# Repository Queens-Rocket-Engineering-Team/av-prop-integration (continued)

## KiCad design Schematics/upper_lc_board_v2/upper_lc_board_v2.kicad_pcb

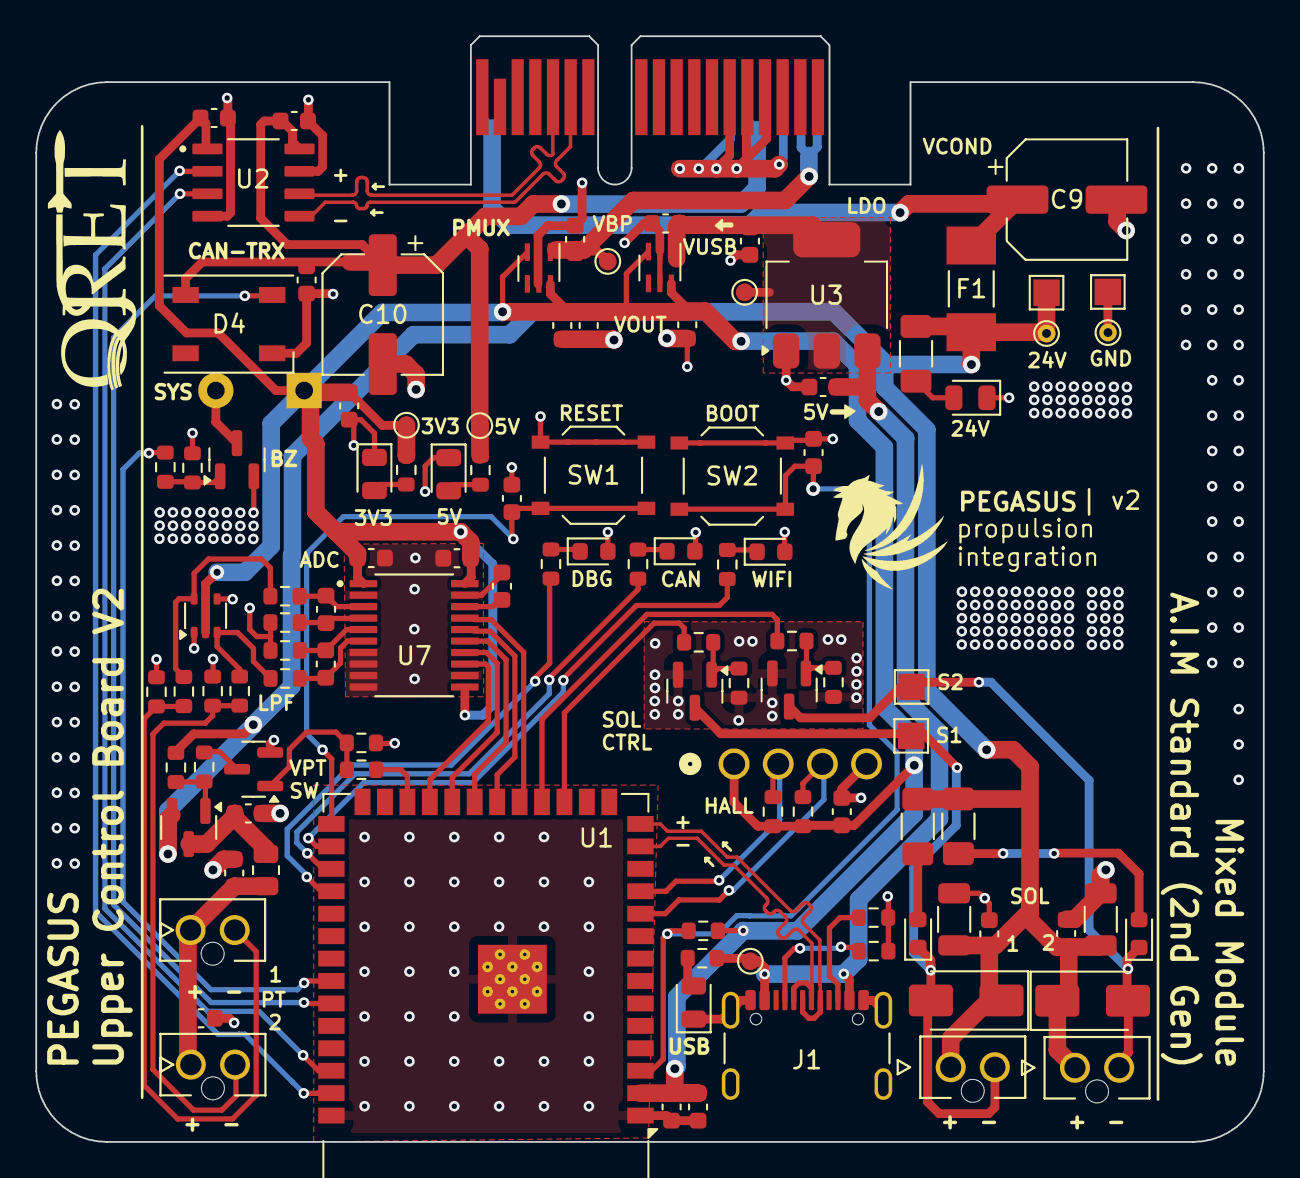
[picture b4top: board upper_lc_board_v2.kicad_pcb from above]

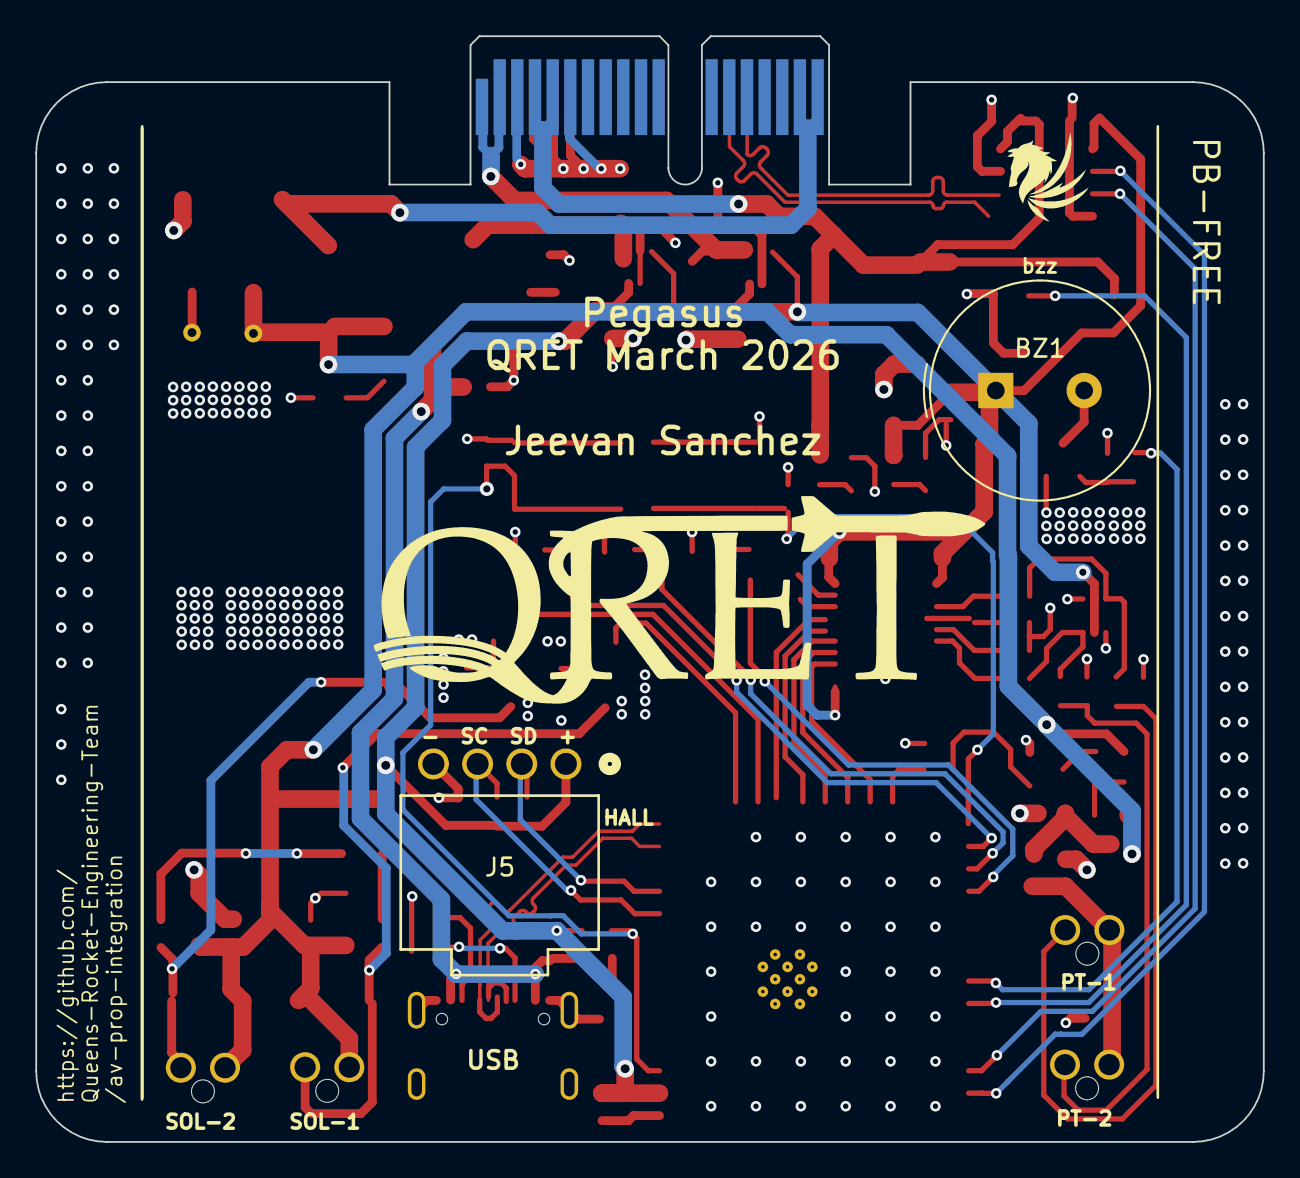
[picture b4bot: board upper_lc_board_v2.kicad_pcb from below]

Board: 4 copper layers, 69.5 x 62.6 mm, 109 parts (2 on the bottom side), 62 nets.

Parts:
BZ1: Buzzer; Buzzer_TDK_PS1240P02BT_D12.2mm_H6.5mm
C1, C11, C12, C29, C31: 1uF; C_0603_1608Metric
C2, C4, C6, C7, C13, C16, C19, C21, C22, C23, C24, C27: 0.1uF; C_0603_1608Metric
C3, C5, C8, C14, C17: 10uF; C_0603_1608Metric
C9: 100uF 35V; CP_Elec_6.3x5.9
C10: 100uF 16V; CP_Elec_6.3x5.9
C15: 1nF; C_0603_1608Metric
C18, C20: 10uF; C_1206_3216Metric
C25, C26: 10nF; C_0603_1608Metric
C30: 220 nF; C_0603_1608Metric
D1: FAULT_LED (RED); LED_0603_1608Metric
D2: CAN_LED (WHT); LED_0603_1608Metric
D3: WIFI_LED (WHT); LED_0603_1608Metric
D4: SYS_LED_WS2812B; LED_WS2812B_PLCC4_5.0x5.0mm_P3.2mm
D5: PWR_3V3_LED (GRN); LED_0805_2012Metric
D6: PWR_24V_LED (GRN); LED_0805_2012Metric
D7: PWR_5V_LED (GRN); LED_0805_2012Metric
D8: USB_LED (GRN); LED_0805_2012Metric
D9: SOL2_LED (WHT); LED_0603_1608Metric
D10: SOL1_LED (WHT); LED_0603_1608Metric
D11: BAV199DW; SOT-363_SC-70-6
D13, D14: SS34; D_SMA
F1: Fuse; FUSC6125X279N
FB1: 100R; R_0805_2012Metric
J1: USB_C_Female_USB2_Small; USB_C_Receptacle_GCT_USB4105-xx-A_16P_TopMnt_Horizontal
J2: Stack Male Edge Connector; BUS_PCIexpress_x1
J3, J4: PT1; MOLEX_1053091102
J5: HALL-1; CONN_SD-105313-100_04_MOL
J6, J7: SOL_CONN; MOLEX_1053091102
Q1, Q2: AO3400A; SOT-23
Q4, Q5: 2N7002; SOT-23
R1, R23, R28, R38: 10k; R_0603_1608Metric
R2: 680; R_0603_1608Metric
R3, R4: 270; R_0603_1608Metric
R5, R6: 5.1k; R_0603_1608Metric
R7: 3.3k; R_0603_1608Metric
R8, R15, R16: 12k; R_1206_3216Metric_Pad1.30x1.75mm_HandSolder
R9, R29, R37: 6.2k; R_0603_1608Metric
R10, R13, R18, R19, R26, R39: 200; R_0603_1608Metric
R11, R14: 62; R_0603_1608Metric
R12, R17: 1k; R_0603_1608Metric
R20, R31: 100k; R_0603_1608Metric
R21, R22: 2.2k; R_0603_1608Metric
R24, R25: 1.2k; R_0603_1608Metric
SW1: SW_ESP_BOOT_MODE; SW_Push_1P1T_XKB_TS-1187A
SW2: SW_ESP_RESET; SW_Push_1P1T_XKB_TS-1187A
TP1: 5V_USB; TestPoint_Pad_D1.0mm
TP2: 3V3-TP; TestPoint_Pad_D1.0mm
TP3: 24V-TP-P; TestPoint_Pad_1.5x1.5mm
TP4: 5V-TP; TestPoint_Pad_D1.0mm
TP5: GND-TP-P; TestPoint_Pad_1.5x1.5mm
TP6: 3V3_BP; TestPoint_Pad_D1.0mm
TP7: GND-TP-H; TestPoint_THTPad_D1.0mm_Drill0.5mm
TP8: VALVE2_OUT_TP; TestPoint_Pad_1.5x1.5mm
TP9: 3V3_USB; TestPoint_Pad_D1.0mm
TP10: VALVE1_OUT_TP; TestPoint_Pad_1.5x1.5mm
TP11: 24V-TP-H; TestPoint_THTPad_D1.0mm_Drill0.5mm
U1: ESP32-S3-WROOM-1-N16; ESP32-S3-WROOM-1
U2: ISO1044BDR; SOIC127P600X175-8N
U3: AMS1117-3.3; SOT-223-3_TabPin2
U4, U5: ID_LM66100DCKR; SC-70-6
U7: ADC_ADS131M04IPWR; SOP65P640X120-20N
U9: DMP4065S-7; SOT-23

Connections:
5V_USB: C14.1, J1.A4 (VBUS), J1.A9 (VBUS), J1.B4 (VBUS), J1.B9 (VBUS), R29.1, TP1.1, U3.3 (VI)
+3V3: BZ1.1 (+), C2.1, C3.1, C6.1, C15.1, C16.1, C17.1, C22.1, C23.1, C29.2, C31.2, D11.2 (K2), D11.5 (K4), J5.1, R1.1, R7.2, R21.2, R22.1, TP2.1, U1.2 (3V3), U2.1 (VCC1), U4.3 (*CE), U4.6 (VOUT), U5.3 (*CE), U5.6 (VOUT), U7.1 (AVDD), U7.11 (~SYNC/~RESET), U7.20 (DVDD)
+5V: C7.1, C10.1, C27.2, D4.1 (VDD), J2.A4 (5.0V_A), J2.A5 (5.0V_A), R9.2, TP4.1, U2.8 (VCC2)
+24V: C18.1, C19.1, C20.1, C21.1, D13.1 (K), D14.1 (K), F1.1, J6.1, J7.1, R8.2, R15.2, R16.2, R37.2, TP3.1, TP11.1, U9.2 (S)
+24V_BP: C9.1, F1.2, J2.A17 (24V_A), J2.A18 (24V_A)
/ESP32-S3 Breakout Circuitry/ESP32_EN: C1.1, R1.2, SW2.2, U1.3 (EN)
/ESP32-S3 Breakout Circuitry/ESP32_IO0: C4.2, SW1.2, U1.27 (IO0)
/ESP32-S3 Breakout Circuitry/GPIO_01: U1.39 (IO1), U2.2 (TXD)
/ESP32-S3 Breakout Circuitry/GPIO_02: U1.38 (IO2), U2.3 (RXD)
/ESP32-S3 Breakout Circuitry/GPIO_35: R4.1, U1.28 (IO35)
/ESP32-S3 Breakout Circuitry/GPIO_36: R3.1, U1.29 (IO36)
/ESP32-S3 Breakout Circuitry/GPIO_37: R2.1, U1.30 (IO37)
/ESP32-S3 Breakout Circuitry/GPIO_42: D4.4 (DIN), U1.35 (IO42)
/ESP32-S3 Breakout Circuitry/USB_N: J1.A7 (D-), J1.B7 (D-), U1.13 (USB_D-)
/ESP32-S3 Breakout Circuitry/USB_P: J1.A6 (D+), J1.B6 (D+), U1.14 (USB_D+)
/Power Circuitry/3V3_BP: C11.2, J2.A1 (3.3V_A), J2.A2 (3.3V_A), TP6.1, U4.1 (VIN)
/Power Circuitry/3V3_USB: C5.1, C12.1, TP9.1, U3.2 (VO), U5.1 (VIN)
/Sensing Circuitry/PT1_CLAMPED: C25.2, R13.1, U7.3 (AIN0P)
/Sensing Circuitry/PT2_CLAMPED: C26.2, R18.1, U7.6 (AIN1P)
ADC_CLKIN: U1.19 (IO11), U7.17 (CLKIN)
ADC_DRDY: U1.23 (IO21), U7.13 (~DRDY)
BUZZ_IN: R10.2, U1.34 (IO41)
CAN_N: J2.B13 (CAN_L), U2.5 (CANL)
CAN_P: J2.B14 (CAN_H), U2.6 (CANH)
GND: C1.2, C2.2, C3.2, C4.1, C5.2, C6.2, C7.2, C8.2, C9.2, C10.2, C11.1, C12.2, C13.2, C14.2, C15.2, C16.2, C17.2, C18.2, C19.2, C20.2, C21.2, C22.2, C23.2, C24.2, C27.1, C29.1, C30.2, C31.1, D1.2 (A), D2.2 (A), D3.2 (A), D4.3 (VSS), D5.1 (K), D6.1 (K), D7.1 (K), D8.1 (K), D11.1 (A1), D11.4 (A3), J1.A1 (GND), J1.A12 (GND), J1.B1 (GND), J1.B12 (GND), J1.S1 (SHIELD), J2.A3 (GND_A), J2.A6 (GND_A), J2.B4 (GND_A), J2.B5 (GND_A), J2.B6 (GND_A), J5.4, Q1.2 (S), Q2.2 (S), Q4.2 (S), Q5.2 (S), R5.2, R6.2, R11.1, R14.1, R20.1, R24.1, R25.1, R28.1, R31.1, R38.1, SW1.1, SW2.1, TP5.1, TP7.1, U1.1 (GND), U1.40 (GND), U1.41 (GND), U2.4 (GND1), U2.7 (GND2), U3.1 (ADJ), U4.2 (GND), U4.5 (ST), U5.2 (GND), U5.5 (ST), U7.2 (AGND), U7.7 (AIN2P), U7.8 (AIN2N), U7.9 (AIN3N), U7.10 (AIN3P), U7.12 (~CS), U7.19 (DGND)
HALL_SCL: J5.3, R22.2, U1.10 (IO17)
HALL_SDA: J5.2, R21.1, U1.11 (IO18)
unnamed: BZ1.2 (-), Q4.3 (D)
unnamed: D1.1 (K), R2.2
unnamed: D2.1 (K), R3.2
unnamed: D3.1 (K), R4.2
unnamed: D5.2 (A), R7.1
unnamed: D6.2 (A), R8.1
unnamed: D7.2 (A), R9.1
unnamed: D8.2 (A), R29.2
unnamed: D9.2 (A), R15.1
unnamed: D10.2 (A), R16.1
unnamed: D11.6 (K3A4), R12.2, R13.2
unnamed: D11.3 (K1A2), R17.2, R18.2
unnamed: J1.A5 (CC1), R5.1
unnamed: J1.B5 (CC2), R6.1
unnamed: J3.2, R14.2, R17.1
unnamed: J4.2, R11.2, R12.1
unnamed: Q1.1 (G), R19.1, R20.2
unnamed: Q2.1 (G), R26.1, R31.2
unnamed: Q4.1 (G), R10.1, R28.2
unnamed: Q5.3 (D), R23.1
unnamed: Q5.1 (G), R38.2, R39.2
unnamed: C25.1, R24.2, U7.4 (AIN0N)
unnamed: C26.1, R25.2, U7.5 (AIN1N)
unnamed: C30.1, U7.18 (CAP)
unnamed: C8.1, FB1.1, U9.3 (D)
unnamed: R23.2, R37.1, U9.1 (G)
SOL1_RET: D10.1 (K), D13.2 (A), J7.2, Q1.3 (D), TP10.1
SOL2_RET: D9.1 (K), D14.2 (A), J6.2, Q2.3 (D), TP8.1
SPI_MISO: U1.21 (IO13), U7.15 (DOUT)
SPI_MOSI: U1.20 (IO12), U7.16 (DIN)
SPI_SCLK: U1.22 (IO14), U7.14 (SCLK)
VALVE1_CTRL: R19.2, U1.17 (IO9)
VALVE2_CTRL: R26.2, U1.18 (IO10)
VPT: C13.1, C24.1, FB1.2, J3.1, J4.1
VPT-SW: R39.1, U1.24 (IO47)

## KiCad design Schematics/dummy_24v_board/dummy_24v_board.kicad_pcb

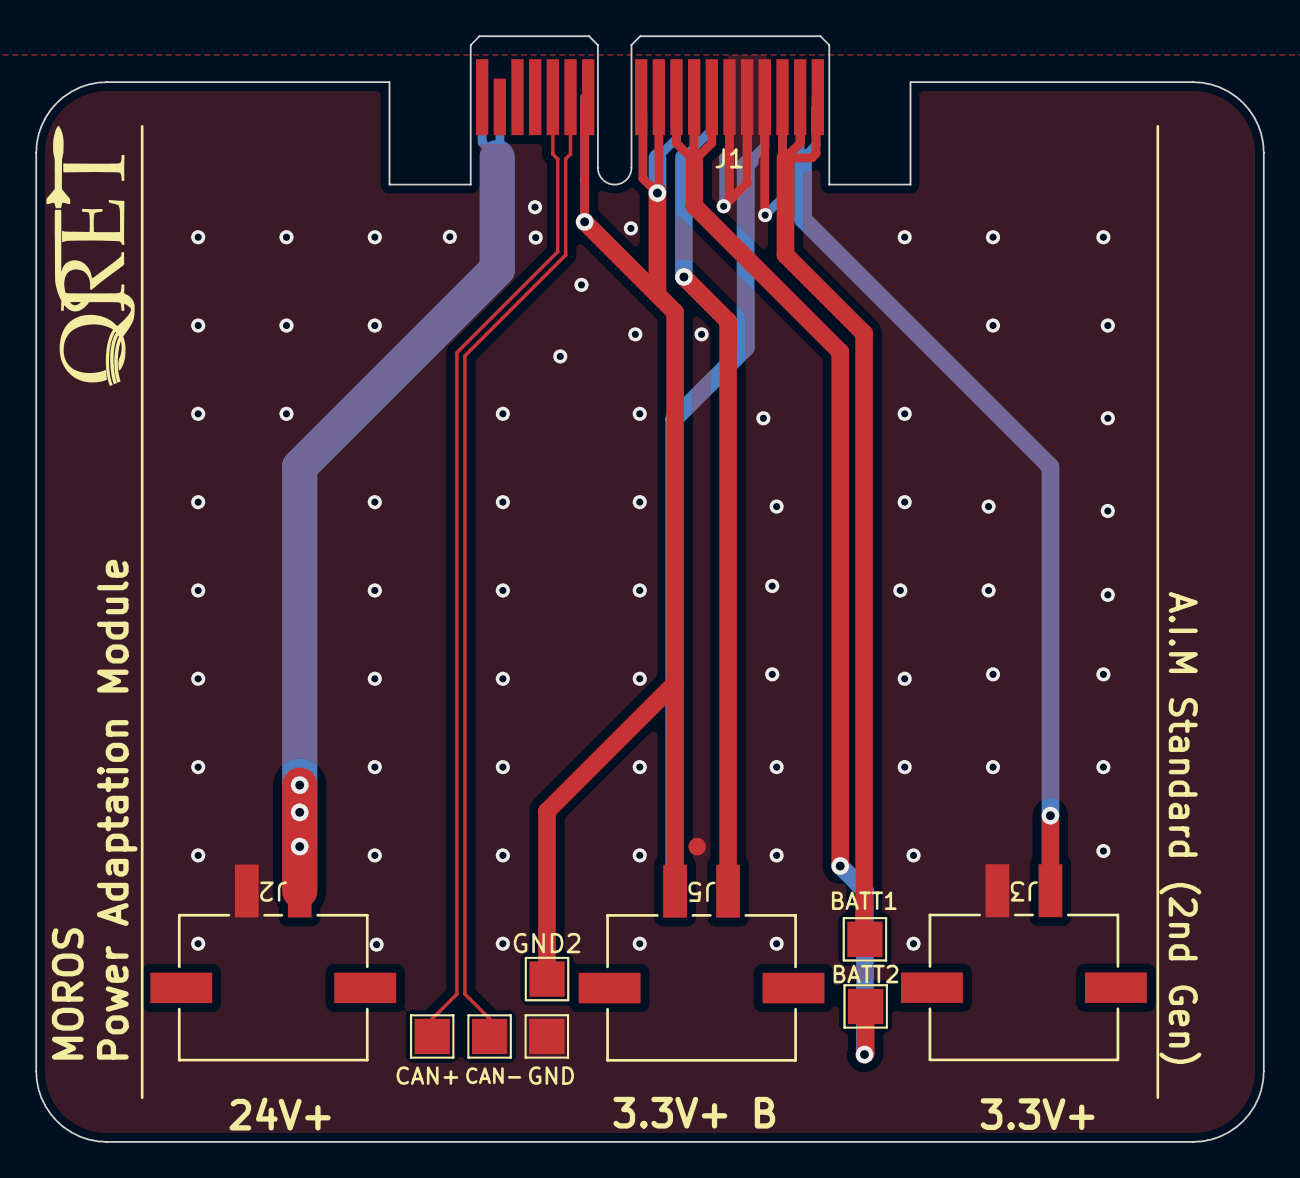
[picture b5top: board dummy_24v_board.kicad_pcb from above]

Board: 2 copper layers, 69.5 x 62.6 mm, 11 parts (1 on the bottom side), 10 nets.

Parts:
BATT1, BATT2: TestPoint; TestPoint_Pad_2.0x2.0mm
CAN+: TestPoint; TestPoint_Pad_2.0x2.0mm
CAN-: TestPoint; TestPoint_Pad_2.0x2.0mm
GND, GND2: TestPoint; TestPoint_Pad_2.0x2.0mm
J1: Stack Male Edge Connector; BUS_PCIexpress_x1
J2, J3, J4, J5: Conn_01x02_Socket; CONN_2-1445057-2_TYCO

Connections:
+3.3V: J1.A1 (3.3V_A), J1.A2 (3.3V_A), J3.1
+3.3V_B: J1.A7 (3.3V_B), J1.A8 (3.3V_B), J5.1
+5V: J1.A4 (5.0V_A), J1.A5 (5.0V_A), J4.1
+24V: J1.A17 (24V_A), J1.A18 (24V_A), J2.1
/BATT_1: BATT1.1, J1.B1 (BATT_A), J1.B2 (BATT_A), J1.B3 (BATT_A)
/BATT_2: BATT2.1, J1.B7 (BATT_B), J1.B8 (BATT_B), J1.B9 (BATT_B)
CAN_+: CAN+.1, J1.B14 (CAN_H)
CAN_-: CAN-.1, J1.B13 (CAN_L)
GND: GND.1, J1.A3 (GND_A), J1.A6 (GND_A), J1.B4 (GND_A), J1.B5 (GND_A), J1.B6 (GND_A), J2.2, J3.2, J4.2
GND2: GND2.1, J1.A9 (GND_B), J1.A12 (GND_B), J1.B10 (GND_B), J1.B11 (GND_B), J1.B12 (GND_B), J5.2

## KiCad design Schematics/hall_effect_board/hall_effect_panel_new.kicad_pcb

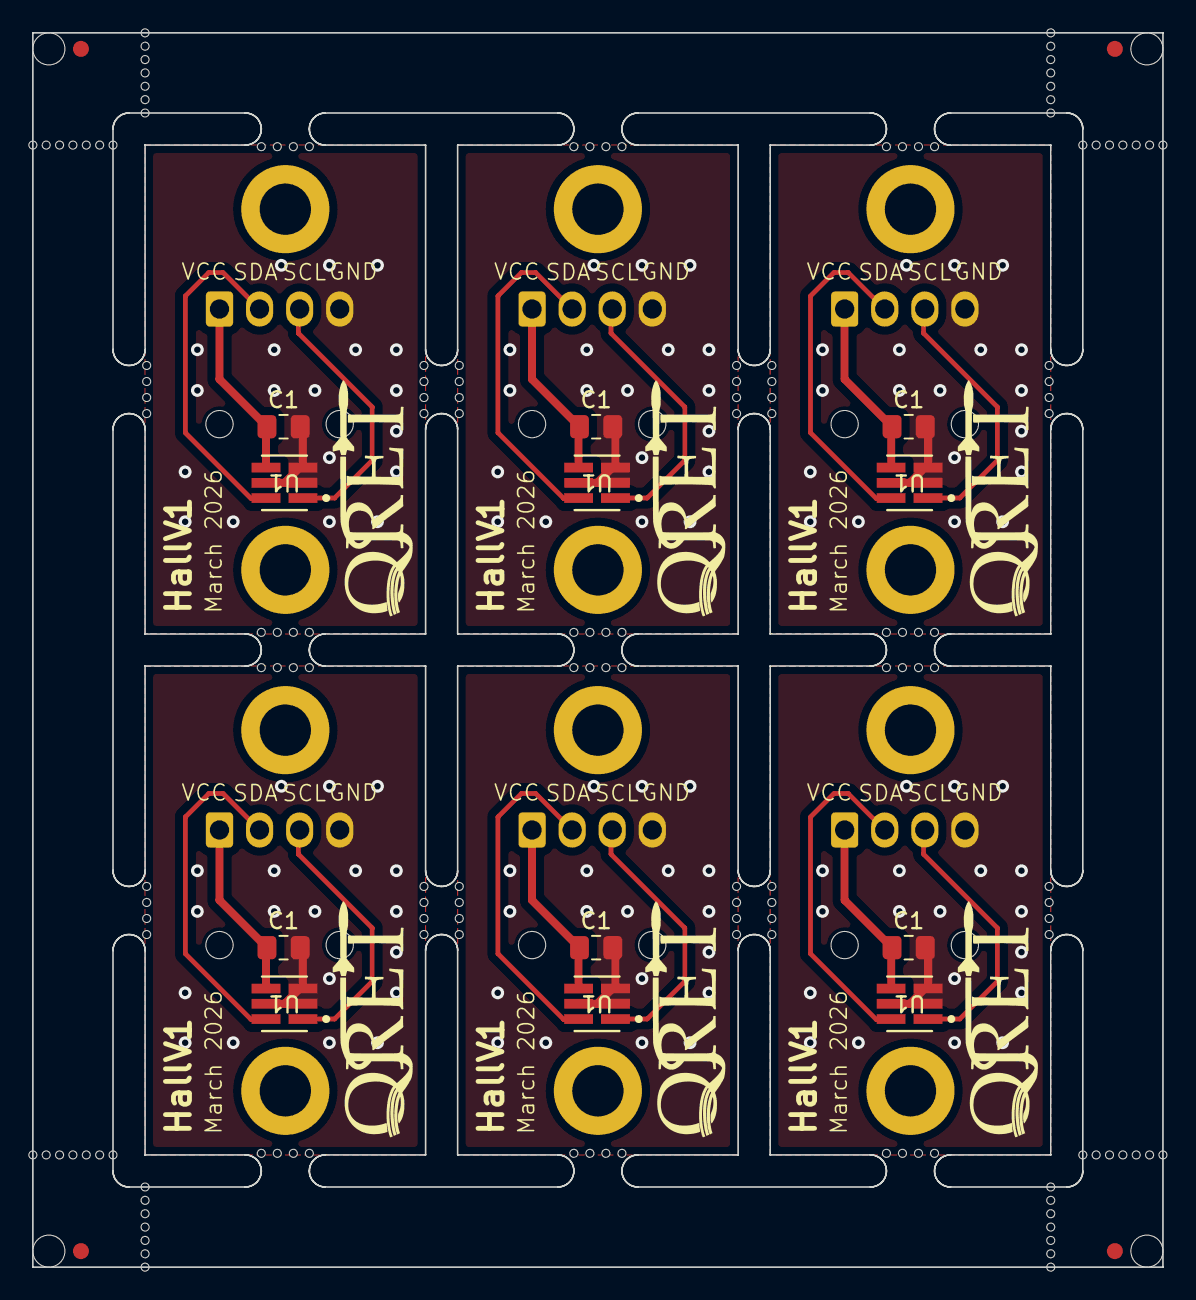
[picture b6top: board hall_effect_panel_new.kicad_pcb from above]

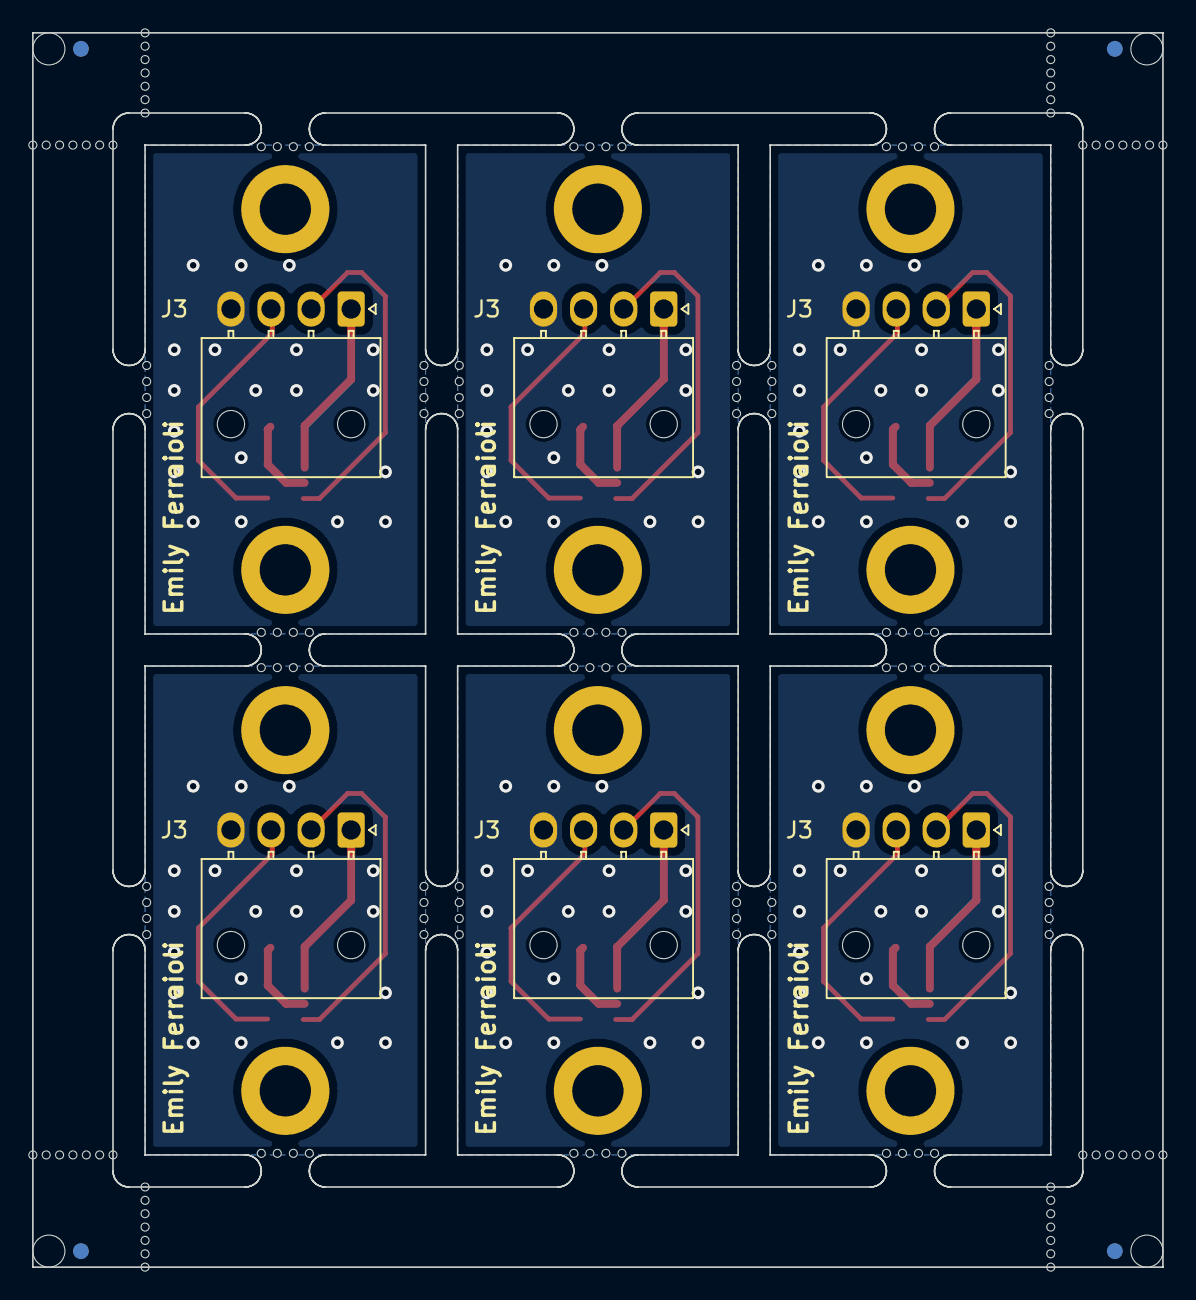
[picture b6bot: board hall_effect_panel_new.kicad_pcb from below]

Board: 2 copper layers, 70.5 x 77.0 mm, 194 parts (10 on the bottom side), 24 nets.

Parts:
C1, C1#2, C1#3, C1#4, C1#5, C1#6: 0.01uF; C_0805_2012Metric_Pad1.18x1.45mm_HandSolder
H1, H1#2, H1#3, H1#4, H1#5, H1#6, H2, H2#2, H2#3, H2#4, H2#5, H2#6: MountingHole; MountingHole_3.2mm_M3_ISO14580_Pad
J3, J3#2, J3#3, J3#4, J3#5, J3#6: HALL-1; Molex_Nano-Fit_105313-xx04_1x04_P2.50mm_Horizontal
KiKit_FID_B_1, KiKit_FID_B_2, KiKit_FID_B_3, KiKit_FID_B_4: Fiducial
KiKit_FID_T_1, KiKit_FID_T_2, KiKit_FID_T_3, KiKit_FID_T_4: Fiducial
KiKit_MB_1_1, KiKit_MB_1_2, KiKit_MB_1_3, KiKit_MB_1_4, KiKit_MB_2_1, KiKit_MB_2_2, KiKit_MB_2_3, KiKit_MB_2_4, KiKit_MB_3_1, KiKit_MB_3_2, KiKit_MB_3_3, KiKit_MB_3_4, KiKit_MB_4_1, KiKit_MB_4_2, KiKit_MB_4_3, KiKit_MB_4_4, KiKit_MB_5_1, KiKit_MB_5_2, KiKit_MB_5_3, KiKit_MB_5_4, KiKit_MB_6_1, KiKit_MB_6_2, KiKit_MB_6_3, KiKit_MB_6_4, KiKit_MB_7_1, KiKit_MB_7_2, KiKit_MB_7_3, KiKit_MB_7_4, KiKit_MB_8_1, KiKit_MB_8_2, KiKit_MB_8_3, KiKit_MB_8_4, KiKit_MB_9_1, KiKit_MB_9_2, KiKit_MB_9_3, KiKit_MB_9_4, KiKit_MB_10_1, KiKit_MB_10_2, KiKit_MB_10_3, KiKit_MB_10_4, KiKit_MB_11_1, KiKit_MB_11_2, KiKit_MB_11_3, KiKit_MB_11_4, KiKit_MB_12_1, KiKit_MB_12_2, KiKit_MB_12_3, KiKit_MB_12_4, KiKit_MB_13_1, KiKit_MB_13_2, KiKit_MB_13_3, KiKit_MB_13_4, KiKit_MB_14_1, KiKit_MB_14_2, KiKit_MB_14_3, KiKit_MB_14_4, KiKit_MB_15_1, KiKit_MB_15_2, KiKit_MB_15_3, KiKit_MB_15_4, KiKit_MB_16_1, KiKit_MB_16_2, KiKit_MB_16_3, KiKit_MB_16_4, KiKit_MB_17_1, KiKit_MB_17_2, KiKit_MB_17_3, KiKit_MB_17_4, KiKit_MB_18_1, KiKit_MB_18_2, KiKit_MB_18_3, KiKit_MB_18_4, KiKit_MB_19_1, KiKit_MB_19_2, KiKit_MB_19_3, KiKit_MB_19_4, KiKit_MB_20_1, KiKit_MB_20_2, KiKit_MB_20_3, KiKit_MB_20_4, KiKit_MB_21_1, KiKit_MB_21_2, KiKit_MB_21_3, KiKit_MB_21_4, KiKit_MB_22_1, KiKit_MB_22_2, KiKit_MB_22_3, KiKit_MB_22_4, KiKit_MB_23_1, KiKit_MB_23_2, KiKit_MB_23_3, KiKit_MB_23_4, KiKit_MB_24_1, KiKit_MB_24_2, KiKit_MB_24_3, KiKit_MB_24_4, KiKit_MB_25_1, KiKit_MB_25_2, KiKit_MB_25_3, KiKit_MB_25_4, KiKit_MB_25_5, KiKit_MB_25_6, KiKit_MB_25_7, KiKit_MB_26_1, KiKit_MB_26_2, KiKit_MB_26_3, KiKit_MB_26_4, KiKit_MB_26_5, KiKit_MB_26_6, KiKit_MB_26_7, KiKit_MB_27_1, KiKit_MB_27_2, KiKit_MB_27_3, KiKit_MB_27_4, KiKit_MB_27_5, KiKit_MB_27_6, KiKit_MB_27_7, KiKit_MB_28_1, KiKit_MB_28_2, KiKit_MB_28_3, KiKit_MB_28_4, KiKit_MB_28_5, KiKit_MB_28_6, KiKit_MB_28_7, KiKit_MB_29_1, KiKit_MB_29_2, KiKit_MB_29_3, KiKit_MB_29_4, KiKit_MB_29_5, KiKit_MB_29_6, KiKit_MB_29_7, KiKit_MB_30_1, KiKit_MB_30_2, KiKit_MB_30_3, KiKit_MB_30_4, KiKit_MB_30_5, KiKit_MB_30_6, KiKit_MB_30_7, KiKit_MB_31_1, KiKit_MB_31_2, KiKit_MB_31_3, KiKit_MB_31_4, KiKit_MB_31_5, KiKit_MB_31_6, KiKit_MB_31_7, KiKit_MB_32_1, KiKit_MB_32_2, KiKit_MB_32_3, KiKit_MB_32_4, KiKit_MB_32_5, KiKit_MB_32_6, KiKit_MB_32_7: NPTH
KiKit_TO_1, KiKit_TO_2, KiKit_TO_3, KiKit_TO_4: NPTH
U1, U1#2, U1#3, U1#4, U1#5, U1#6: TMAG5273A1QDBVT; DBV0006A-IPC_A

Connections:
Board_0-+3V3: C1#4.1, J3#4.1, U1#4.4 (VCC)
Board_0-GND: C1#4.2, J3#4.4, U1#4.2 (TEST), U1#4.3 (GND), U1#4.5 (INT_N)
Board_0-SCA: J3#4.2, U1#4.6 (SDA)
Board_0-SCL: J3#4.3, U1#4.1 (SCL)
Board_1-+3V3: C1#3.1, J3#2.1, U1.4 (VCC)
Board_1-GND: C1#3.2, J3#2.4, U1.2 (TEST), U1.3 (GND), U1.5 (INT_N)
Board_1-SCA: J3#2.2, U1.6 (SDA)
Board_1-SCL: J3#2.3, U1.1 (SCL)
Board_2-+3V3: C1#5.1, J3.1, U1#2.4 (VCC)
Board_2-GND: C1#5.2, J3.4, U1#2.2 (TEST), U1#2.3 (GND), U1#2.5 (INT_N)
Board_2-SCA: J3.2, U1#2.6 (SDA)
Board_2-SCL: J3.3, U1#2.1 (SCL)
Board_3-+3V3: C1#6.1, J3#5.1, U1#6.4 (VCC)
Board_3-GND: C1#6.2, J3#5.4, U1#6.2 (TEST), U1#6.3 (GND), U1#6.5 (INT_N)
Board_3-SCA: J3#5.2, U1#6.6 (SDA)
Board_3-SCL: J3#5.3, U1#6.1 (SCL)
Board_4-+3V3: C1#2.1, J3#6.1, U1#5.4 (VCC)
Board_4-GND: C1#2.2, J3#6.4, U1#5.2 (TEST), U1#5.3 (GND), U1#5.5 (INT_N)
Board_4-SCA: J3#6.2, U1#5.6 (SDA)
Board_4-SCL: J3#6.3, U1#5.1 (SCL)
Board_5-+3V3: C1.1, J3#3.1, U1#3.4 (VCC)
Board_5-GND: C1.2, J3#3.4, U1#3.2 (TEST), U1#3.3 (GND), U1#3.5 (INT_N)
Board_5-SCA: J3#3.2, U1#3.6 (SDA)
Board_5-SCL: J3#3.3, U1#3.1 (SCL)

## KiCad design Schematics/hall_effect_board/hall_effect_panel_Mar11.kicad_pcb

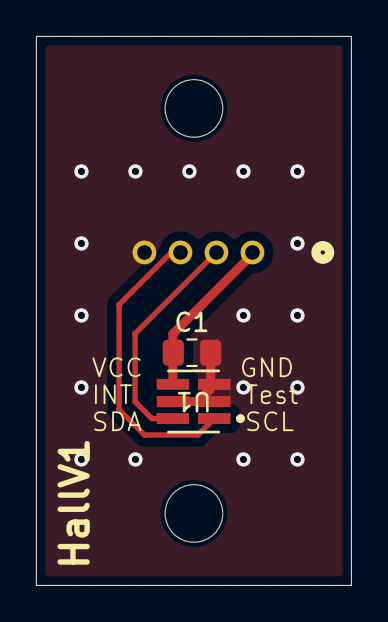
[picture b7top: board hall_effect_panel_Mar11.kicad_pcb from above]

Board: 2 copper layers, 17.5 x 30.5 mm, 5 parts (1 on the bottom side), 4 nets.

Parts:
C1: 0.01uF; C_0805_2012Metric_Pad1.18x1.45mm_HandSolder
H1, H2: MountingHole; MountingHole_3.2mm_M3
J1: B04B-PASK; CONN_B04B-PASK_JST
U1: TMAG5273A1QDBVT; DBV0006A-IPC_A

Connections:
+3V3: C1.1, J1.1, U1.4 (VCC)
GND: C1.2, J1.4, U1.2 (TEST), U1.3 (GND), U1.5 (INT_N)
SCA: J1.3, U1.6 (SDA)
SCL: J1.2, U1.1 (SCL)

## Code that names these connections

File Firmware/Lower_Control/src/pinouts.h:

// Header file containing pinouts for this module 

#ifndef PINOUT_H
#define PINOUT_H

#define FL_CS_PIN PB0
#define VSOL_SENSE_PIN PB1
#define CAN_LED_PIN PB4
#define RGB_DATA_PIN PB5

// I2C-1 BUS
#define HALL_SCL1_PIN PB6
#define HALL_SDA1_PIN PB7

#define CAN_RX_PIN PB8
#define CAN_TX_PIN PB9

// I2C-2 BUS
#define HALL_SCL2_PIN PB10
#define HALL_SDA2_PIN PB11

#define RESET_FL_PIN PB12
#define SOL1_EN_PIN PB13
#define SOL2_EN_PIN PB14

#define ADC_CLKIN_PIN PA0
#define ADC_DRDY_PIN PA1
#define VPT_EN_PIN PA2
#define ADC_CS_PIN PA3
#define CJC_SENSE_PIN PA4 // adc12_in4

// SPI-1 BUS (ADC & FLASH MODULE)
#define SPI_SCLK_PIN PA5
#define SPI_MISO_PIN PA6
#define SPI_MOSI_PIN PA7

#define DB_LED_PIN PA8

// USART-1 (swapped cause of hardware issue)
#define USART_TX_PIN PA10
#define USART_RX_PIN PA9

#define VSOL_EN_PIN PA11

// SW DEBUG
#define SWDIO_PIN PA13
#define SWCLK_PIN PA14

#endif

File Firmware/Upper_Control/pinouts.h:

// Header file containing pinouts for this module 

#define CAN_TX_PIN 1 
#define CAN_RX_PIN 2 
#define SENSE_24V_PIN 7 
#define SOL1_EN_PIN 9
#define SOL2_EN_PIN 10

// ADC SPI
#define ADC_CLKIN_PIN 11
#define ADC_MOSI_PIN 12
#define ADC_MISO_PIN 13
#define ADC_SCLK_PIN 14

// HALL I2C 
#define HALL_SCL_PIN 17
#define HALL_SDA_PIN 18

#define ADC_DRDY_PIN 19

// iterable
const int WIFI_LED_PIN 35
const int CAN_LED_PIN 36
const int DEBUG_LED_PIN 37

#define BUZZ_EN_PIN 41
#define RGB_DATA_PIN 42
#define VPT_EN_PIN 47

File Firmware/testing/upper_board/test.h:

// future pinout for reference, prob wont use for testing

const int  PT1_LED=  36;
const int  PT2_LED =  35;
const int  HALL_LED = 37;
const int  TC_LED = 48;
const int  CAN_LED = 41;
const int  WIFI_LED = 40;
const int  FAULT_LED =  42;

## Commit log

2026-01-12 add requested changes for PR
2026-01-14 add all circuitry and missing datasheets
2026-01-18 pin assignments verified
2026-01-18 start layout
2026-01-18 replace sensing LEDs with a single
2026-01-18 quick changes
2026-01-18 init commit of board that provides 24V for testing
2026-01-18 layout work
    #TODO
    - smaller 3V3 buck, add HF cap
    - finish layout
2026-01-18 Board setup with footprint
2026-01-20 layout work
2026-01-20 add sensing circuitry layout
2026-01-20 finish layout
    - model paths need to be fixed
    - waiting for confirmation for shared folders
2026-01-22 added 3.3V,5V,CAN
2026-01-22 add power switching for PTs (schematic only)
2026-01-26 more layout work, add testing code
2026-01-26 add buzzer circuitry, some layout work
2026-01-27 some routing work
2026-01-28 CAN, JTAG & I2C routing
2026-01-28 start power routing
2026-01-28 added two TestPoints for BATT 1&2
2026-01-29 quick push
2026-01-29 quick revert for layout cleanup
2026-01-30 add new package to schwmatic
2026-01-31 organizational work
2026-02-01 more organizational work, add shared footprint, model, symbol dirs and clean up individuals
2026-02-01 routing work
2026-02-01 gnd vias added
2026-02-01 Vias modified
2026-02-01 Connectors model added
2026-02-03 via sizes changed
2026-02-03 cleanup PCB, switch to solid copper pour, add GND tp, and updated silkscreen
2026-02-04 more routing work
2026-02-04 ADC routing
2026-02-04 single finished hall effect
    -need to fix connector step orientation
2026-02-05 testing work
2026-02-07 analog routing, start 3V3 power routing
2026-02-08 more 3v3 routing
    - considering ground pour on f.cu for mosfet src
    - reconsidering multiple gnd nets
2026-02-08 remove AGND
    simplicity
2026-02-09 quick
2026-02-11 remove ai slop
2026-02-12 ADC testing
    - update testing FW with new ADC lib
    - switched 165 shunt resistor to 60 based on fixed calculations
2026-02-18 working thermister and thermocouple prototype
2026-02-20 adjust routing for 0603 min. footprints
2026-02-21 more local pours and 0402 adjustments
2026-02-21 fix CAN transceiver model
2026-02-25 review of schematics and pcb
    - verified all STM pins
    - reviewed all circuits
    - reviewed trace clearences, made sure routes are connected, etc.
2026-02-25 silkscreen
2026-02-26 WIP-commit: remove surge prot, move TH to back-side.
2026-02-28 remove surge protector
2026-02-28 put TH on backside, add edge-vias
2026-02-28 finalize additional gnd hole
    - added a tht gnd TP in addition to pad for easier testingr
2026-03-01 new backplane connector
2026-03-01 review changes
2026-03-01 start of review for lower control board, Cleaning up power and spi traces
2026-03-05 review work
2026-03-05 cleanup
2026-03-05 updates to dummy board for splitting A and B power and new edge connector
2026-03-07 schematic setup
2026-03-07 Updated PCB layout with new 3.3V_B connector
2026-03-08 pcb design
2026-03-09 add additional LEDs
2026-03-10 3.3V_B flipped to front & Gn2 trace added
2026-03-10 add silkscreen
2026-03-10 gnd pour
2026-03-11 small adjusmetns
2026-03-11 add gnd pour
2026-03-11 pmux fix
2026-03-11 DRC checked
2026-03-11 shifted 5V molex
2026-03-11 final updates before putting in cart
2026-03-12 Single hall effect sensor with fixed via and text
2026-03-12 Completed hall effect panel with fixed vias
2026-03-16 increase width on power rails from USB and SWD, start tuning diff pairs
2026-03-16 tune diff pairs, increase track width on 5V rail
2026-03-18 cleaned up hall effect, switched to plated through holes
2026-03-18 start lower refactor
2026-03-19 Update LLibraryfor 3.3v Line B
2026-03-23 organize working copy of lower valve board for merge to main
2026-03-23 clean merge artifacts
2026-03-25 refactor with new conns
2026-03-25 layout updates after review, cleaned up schematic organization
2026-03-25 update for emily!!
2026-03-26 Hall effect panel for updated connector
2026-03-26 swap I2C lines, add digi numbers to conns, fix diode issue
2026-03-27 lower refactor for review
    - curr using horziontal screw for TC
2026-03-27 resolve DRC & tweak
2026-03-27 update with new TC screw terminal
2026-03-28 update schematic pin names
2026-03-28 updated part numbers and fixed minor circuit issues
2026-03-28 update backplane orientation
2026-03-28 updated pcb after part number and schematic fixes
2026-03-28 PCB for review
2026-03-28 WIP - i2c-2 refactor
2026-03-28 updated silkscree and changed PI caps
2026-03-28 start routing for new bus
2026-03-28 start 2nd refactor
2026-03-28 silkscreen and new i2c bus
2026-03-28 final silkscreen
2026-03-28 change TP footprint for consistency across boards
2026-03-28 silk
2026-03-29 move lc v2 to og folder
2026-03-29 Footprint Update
2026-03-30 Silkscreen update
2026-03-30 New Paneled PCB
2026-03-30 final upper control board
2026-03-30 actual final updates
2026-03-30 final upper control board in cart, fixed HALL connector
2026-03-30 added 24V sensing to upper board
2026-03-31 Add LED
2026-03-31 updates and added to cart
2026-04-05 replace old part number, clean up old design comments
2026-04-11 updated main and schematics READMEs
2026-04-11 added documentation for firmware and platformIO instructions
2026-04-11 add board-specifc READMEs (TODO), cleanup schematic titles
2026-04-11 Update README.md
    Updated README to improve formatting and usage instructions.
2026-04-11 outline README files for boards
2026-04-12 added overview and revision history sections
2026-04-12 document power management circuitry
2026-04-13 added valve control section
2026-04-14 documented sensing circuitry
2026-04-14 document MCU breakout circuitry for both boards
2026-04-14 documented board design stuff
2026-04-14 final doc changes (formatting)
2026-04-15 updated and migrated testing code into library (prop_testing)
2026-04-15 updated bool name for mode select
2026-04-18 add ed pinouts
2026-04-19 wrote upper testing code
2026-04-19 added lower testing code
2026-04-19 add register defs
2026-04-19 folder chnge
2026-04-24 finish ADC lib
2026-04-24 adjust sensor control flow for ADC lib
2026-04-24 add clock setup to board-specific tests
2026-04-24 added hall code with temp. library
2026-04-24 add hall testing to prop_testing and upper
2026-04-25 testing changes
2026-04-27 added comments to lower testing code
2026-04-28 Fix formatting issue in README.md
2026-04-30 setup folders for TMAG5273 lib
2026-05-04 lib setup & register defs
2026-05-05 add board imgs
2026-05-05 read/write register function implemenmtatojs
2026-05-05 init function
2026-05-06 added some helper functions
2026-05-06 main implementation
2026-05-06 added simple example
2026-05-06 added basic read example for ADS131M04 library
2026-05-07 start readmes
2026-05-07 documented HALL libary
2026-05-07 documented ADC library and updated test codes with hall library
2026-05-07 documented testing lib
2026-05-10 Found issue on hall board, only effects LED
2026-05-17 moved testing code
2026-05-17 begin integration with LC: using ArimNetwork "0.4.0", untested, rushed commit to get others involved - needs heavy testing and refinement - wifi code comes directly from prop-esp32-logger/esp-idf bra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
